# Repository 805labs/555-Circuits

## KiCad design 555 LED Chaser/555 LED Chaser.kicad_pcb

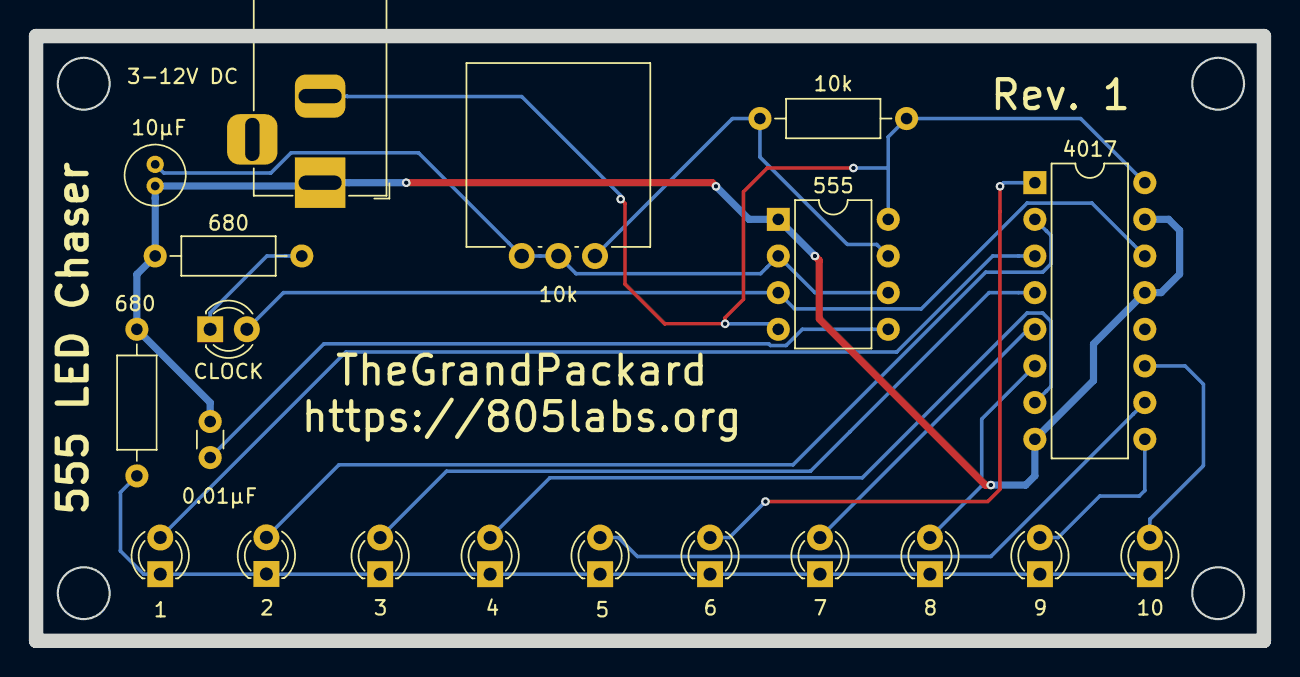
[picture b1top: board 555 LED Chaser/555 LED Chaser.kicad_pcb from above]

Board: 2 copper layers, 85.1 x 41.9 mm, 20 parts (0 on the bottom side), 18 nets.

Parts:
0.01μF: 0.01μF; C_Disc_D3.0mm_W1.6mm_P2.50mm
1: 1; LED_D3.0mm
2: 2; LED_D3.0mm
3: 3; LED_D3.0mm
3-12V DC: 5-9V DC; BarrelJack_Horizontal
4: 4; LED_D3.0mm
5: 5; LED_D3.0mm
6: 6; LED_D3.0mm
7: 7; LED_D3.0mm
8: 8; LED_D3.0mm
9: 9; LED_D3.0mm
10: 10; LED_D3.0mm
10k: 10k; R_Axial_DIN0207_L6.3mm_D2.5mm_P10.16mm_Horizontal
10k#2: 10k; Potentiometer_Vishay_148-149_Single_Vertical
10μF: 10μF; C_Radial_D4.0mm_H5.0mm_P1.50mm
555: 555; DIP-8_W7.62mm
680, 680#2: 680; R_Axial_DIN0207_L6.3mm_D2.5mm_P10.16mm_Horizontal
4017: 4017; DIP-16_W7.62mm
CLOCK: CLOCK; LED_D3.0mm

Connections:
unnamed: 10k#2.2, 10k#2.3, 10μF.1, 555.2, 555.6
unnamed: 0.01μF.2, 3-12V DC.1, 10μF.2, 555.1, 680.2, 680#2.2, 4017.8, 4017.13, 4017.15
unnamed: 0.01μF.1, 555.5
unnamed: 680.1, CLOCK.1
unnamed: 555.3, 4017.14, CLOCK.2
unnamed: 1.2, 4017.3
unnamed: 2.2, 4017.2
unnamed: 3.2, 4017.4
unnamed: 4.2, 4017.7
unnamed: 5.2, 4017.10
unnamed: 6.2, 4017.1
unnamed: 7.2, 4017.5
unnamed: 8.2, 4017.6
unnamed: 1.1, 2.1, 3.1, 4.1, 5.1, 6.1, 7.1, 8.1, 9.1, 10.1, 680#2.1
unnamed: 9.2, 4017.9
unnamed: 10.2, 4017.11
unnamed: 3-12V DC.2, 10k.1, 555.4, 555.8, 4017.16
unnamed: 10k.2, 10k#2.1, 555.7

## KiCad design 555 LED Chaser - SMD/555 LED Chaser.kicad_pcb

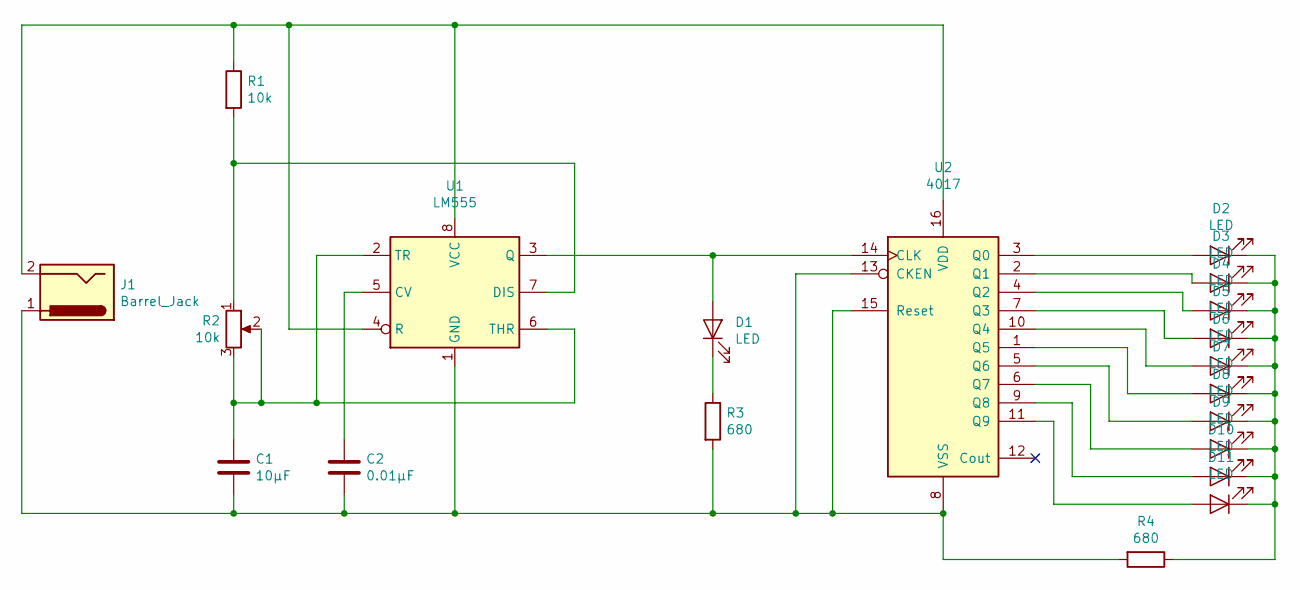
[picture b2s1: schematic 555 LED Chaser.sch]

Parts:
C1: 10μF; C_1206
C2: 0.01μF; C_0603
D1, D2, D3, D4, D5, D6, D7, D8, D9, D10, D11: LED; LED_0805
J1: Barrel_Jack; Pin_Header_Straight_1x02_Pitch2.54mm_SMD_Pin1Left
R1: 10k; R_0603
R2: 10k; Potentiometer_Trimmer-EVM3E
R3, R4: 680; R_0603
U1: LM555; SO-8_5.3x6.2mm_Pitch1.27mm
U2: 4017; SOIC-16_3.9x9.9mm_Pitch1.27mm

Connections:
unnamed: C1.1, R2.2, R2.3, U1.2 (TR), U1.6 (THR)
unnamed: C1.2, C2.2, J1.1, R3.2, R4.2, U1.1 (GND), U2.8 (VSS), U2.13 (CKEN), U2.15 (Reset)
unnamed: C2.1, U1.5 (CV)
unnamed: D1.1 (K), R3.1
unnamed: D1.2 (A), U1.3 (Q), U2.14 (CLK)
unnamed: D2.2 (A), U2.3 (Q0)
unnamed: D3.2 (A), U2.2 (Q1)
unnamed: D4.2 (A), U2.4 (Q2)
unnamed: D5.2 (A), U2.7 (Q3)
unnamed: D6.2 (A), U2.10 (Q4)
unnamed: D7.2 (A), U2.1 (Q5)
unnamed: D8.2 (A), U2.5 (Q6)
unnamed: D9.2 (A), U2.6 (Q7)
unnamed: D2.1 (K), D3.1 (K), D4.1 (K), D5.1 (K), D6.1 (K), D7.1 (K), D8.1 (K), D9.1 (K), D10.1 (K), D11.1 (K), R4.1
unnamed: D10.2 (A), U2.9 (Q8)
unnamed: D11.2 (A), U2.11 (Q9)
unnamed: J1.2, R1.1, U1.4 (R), U1.8 (VCC), U2.16 (VDD)
unnamed: R1.2, R2.1, U1.7 (DIS)

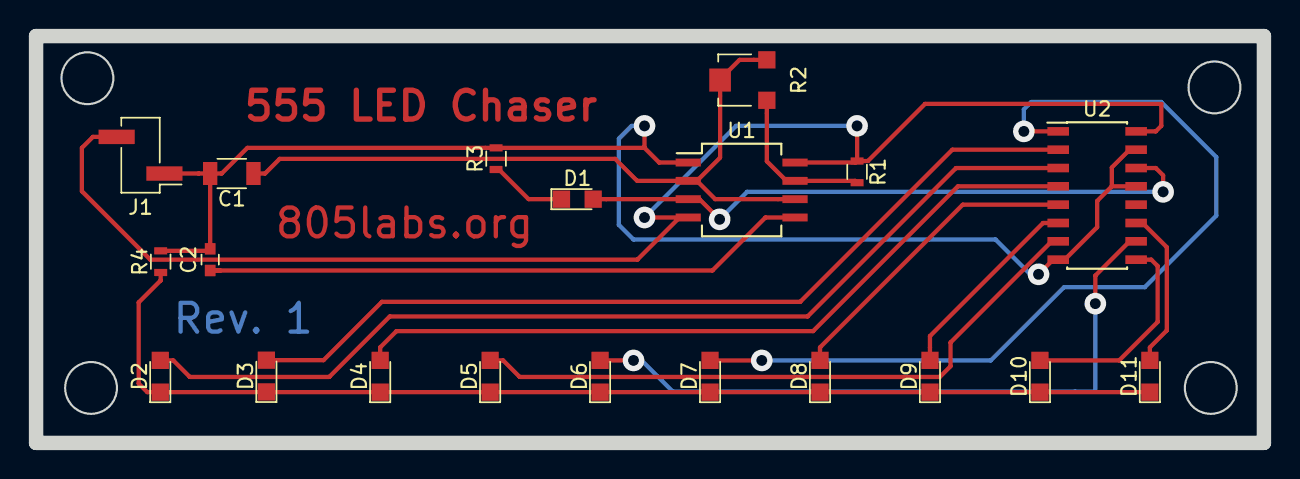
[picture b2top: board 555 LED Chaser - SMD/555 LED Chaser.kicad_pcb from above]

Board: 2 copper layers, 85.1 x 28.2 mm, 20 parts (0 on the bottom side), 18 nets.

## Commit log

2019-04-14 Modified traces to be 1mm wide for better vinyl printing
2019-04-24 Updated pcb layout
2019-04-24 Added new design
2019-04-24 Final tweaks before submitting to fabrication
